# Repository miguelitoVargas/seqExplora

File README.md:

# seqExplora
modulos tarjetas kicad

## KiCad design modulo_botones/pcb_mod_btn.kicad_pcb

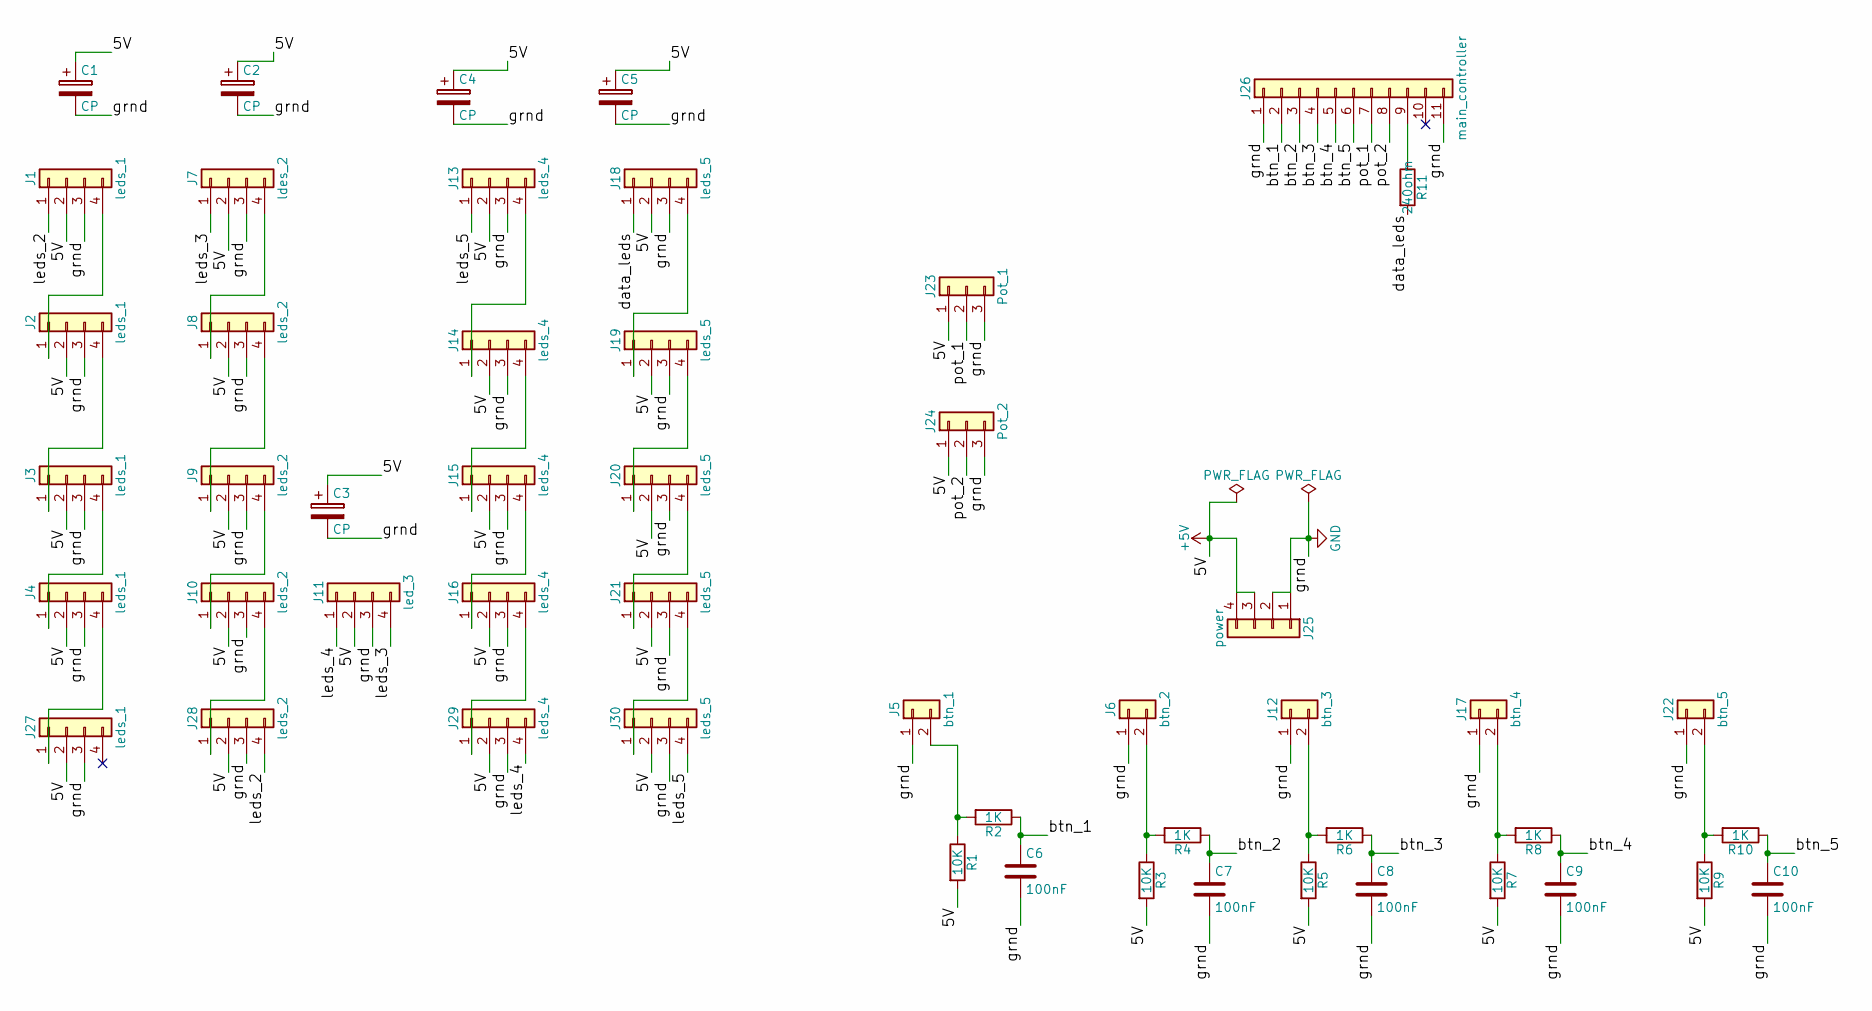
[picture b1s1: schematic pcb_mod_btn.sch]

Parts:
C1, C2, C3, C4, C5: CP; CP_Radial_D8.0mm_P5.00mm
C6, C7, C8, C9, C10: 100nF; C_0805_HandSoldering
J1, J2, J3, J4, J27: leds_1; Pin_Header_Straight_1x04_Pitch2.54mm
J5: btn_1; Pin_Header_Straight_1x02_Pitch2.54mm
J6: btn_2; Pin_Header_Straight_1x02_Pitch2.54mm
J7: ldes_2; Pin_Header_Straight_1x04_Pitch2.54mm
J8, J9, J10, J28: leds_2; Pin_Header_Straight_1x04_Pitch2.54mm
J11: led_3; Pin_Header_Straight_1x04_Pitch2.54mm
J12: btn_3; Pin_Header_Straight_1x02_Pitch2.54mm
J13, J14, J15, J16, J29: leds_4; Pin_Header_Straight_1x04_Pitch2.54mm
J17: btn_4; Pin_Header_Straight_1x02_Pitch2.54mm
J18, J19, J20, J21, J30: leds_5; Pin_Header_Straight_1x04_Pitch2.54mm
J22: btn_5; Pin_Header_Straight_1x02_Pitch2.54mm
J23: Pot_1; Pin_Header_Straight_1x03_Pitch2.54mm
J24: Pot_2; Pin_Header_Straight_1x03_Pitch2.54mm
J25: power; TerminalBlock_bornier-4_P5.08mm
J26: main_controller; Pin_Header_Straight_1x11_Pitch2.54mm
R1, R3, R5, R7, R9: 10K; R_0805_HandSoldering
R2, R4, R6, R8, R10: 1K; R_0805_HandSoldering
R11: 240ohm; R_0805_HandSoldering

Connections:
+5V: C1.1, C2.1, C3.1, C4.1, C5.1, J1.2, J2.2, J3.2, J4.2, J7.2, J8.2, J9.2, J10.2, J11.2, J13.2, J14.2, J15.2, J16.2, J18.2, J19.2, J20.2, J21.2, J23.1, J24.1, J25.3, J25.4, J27.2, J28.2, J29.2, J30.2, R1.2, R3.2, R5.2, R7.2, R9.2
/btn_1: C6.1, J26.2, R2.1
/btn_2: C7.1, J26.3, R4.1
/btn_3: C8.1, J26.4, R6.1
/btn_4: C9.1, J26.5, R8.1
/btn_5: C10.1, J26.6, R10.1
/data_leds: J18.1, R11.2
/leds_2: J1.1, J28.4
/leds_3: J7.1, J11.4
/leds_4: J11.1, J29.4
/leds_5: J13.1, J30.4
/pot_1: J23.2, J26.7
/pot_2: J24.2, J26.8
GND: C1.2, C2.2, C3.2, C4.2, C5.2, C6.2, C7.2, C8.2, C9.2, C10.2, J1.3, J2.3, J3.3, J4.3, J5.1, J6.1, J7.3, J8.3, J9.3, J10.3, J11.3, J12.1, J13.3, J14.3, J15.3, J16.3, J17.1, J18.3, J19.3, J20.3, J21.3, J22.1, J23.3, J24.3, J25.1, J25.2, J26.1, J26.11, J27.3, J28.3, J29.3, J30.3
unnamed: J1.4, J2.1
unnamed: J2.4, J3.1
unnamed: J3.4, J4.1
unnamed: J5.2, R1.1, R2.2
unnamed: J6.2, R3.1, R4.2
unnamed: J7.4, J8.1
unnamed: J8.4, J9.1
unnamed: J9.4, J10.1
unnamed: J10.4, J28.1
unnamed: J12.2, R5.1, R6.2
unnamed: J13.4, J14.1
unnamed: J14.4, J15.1
unnamed: J15.4, J16.1
unnamed: J16.4, J29.1
unnamed: J17.2, R7.1, R8.2
unnamed: J18.4, J19.1
unnamed: J19.4, J20.1
unnamed: J20.4, J21.1
unnamed: J21.4, J30.1
unnamed: J22.2, R9.1, R10.2
unnamed: J26.9, R11.1
unnamed: J4.4, J27.1

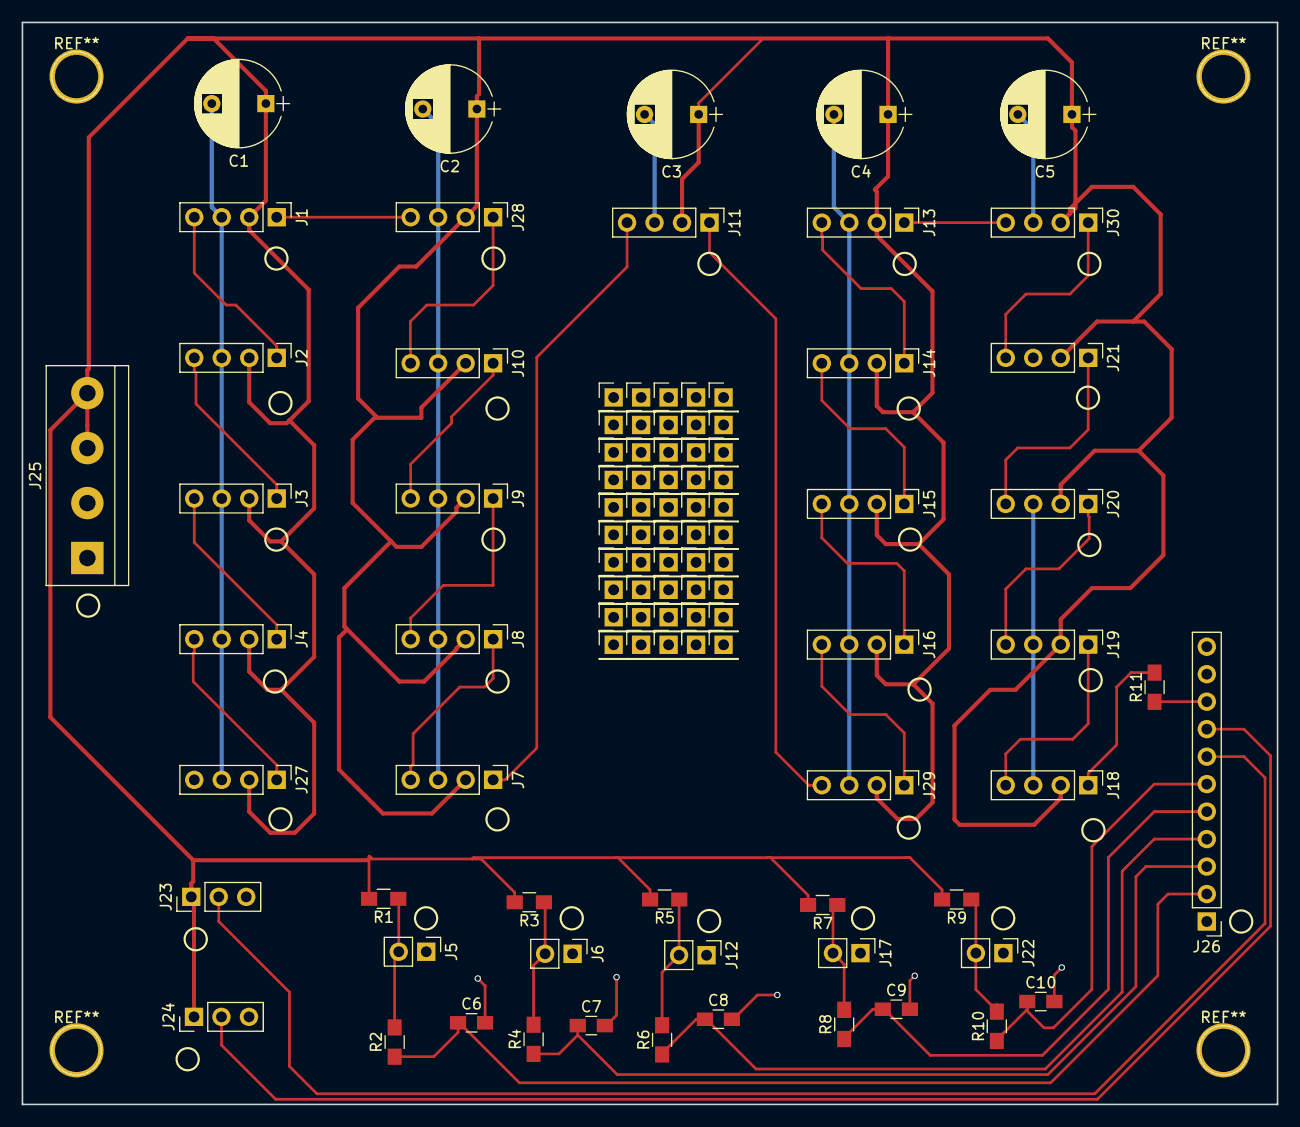
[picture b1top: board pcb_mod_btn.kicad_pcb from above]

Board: 2 copper layers, 116.0 x 100.0 mm, 51 parts (0 on the bottom side), 36 nets.

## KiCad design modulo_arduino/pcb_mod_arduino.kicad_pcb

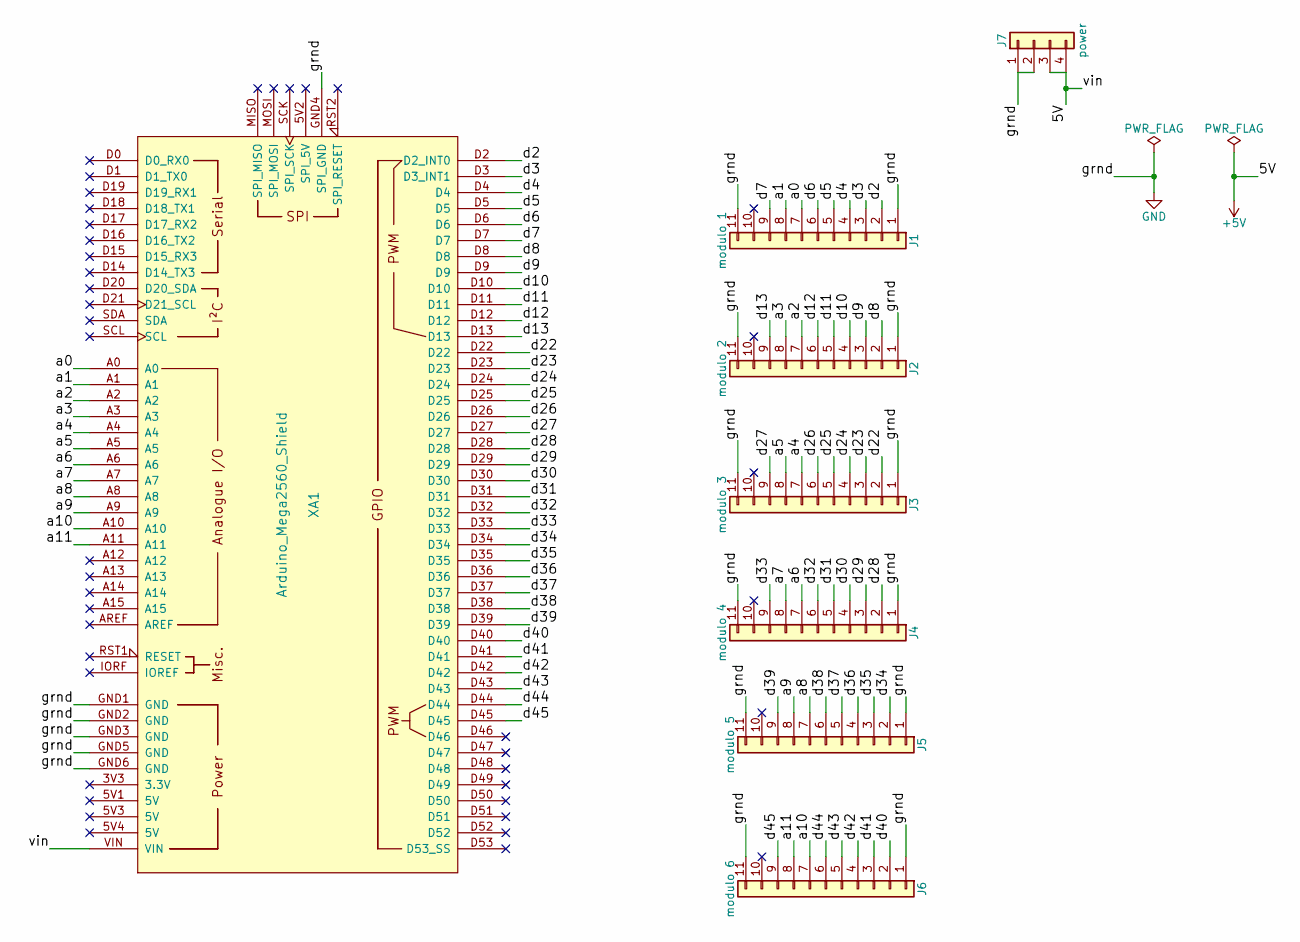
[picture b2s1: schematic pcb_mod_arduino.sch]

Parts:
J1: modulo 1; Pin_Header_Straight_1x11_Pitch2.54mm
J2: modulo 2; Pin_Header_Straight_1x11_Pitch2.54mm
J3: modulo 3; Pin_Header_Straight_1x11_Pitch2.54mm
J4: modulo 4; Pin_Header_Straight_1x11_Pitch2.54mm
J5: modulo 5; Pin_Header_Straight_1x11_Pitch2.54mm
J6: modulo 6; Pin_Header_Straight_1x11_Pitch2.54mm
J7: power; TerminalBlock_bornier-4_P5.08mm
XA1: Arduino_Mega2560_Shield

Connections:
+5V: J7.3, J7.4, XA1.VIN
/a0: J1.7, XA1.A0
/a1: J1.8, XA1.A1
/a2: J2.7, XA1.A2
/a3: J2.8, XA1.A3
/a4: J3.7, XA1.A4
/a5: J3.8, XA1.A5
/a6: J4.7, XA1.A6
/a7: J4.8, XA1.A7
/a8: J5.7, XA1.A8
/a9: J5.8, XA1.A9
/a10: J6.7, XA1.A10
/a11: J6.8, XA1.A11
/d2: J1.2, XA1.D2 (D2_INT0)
/d3: J1.3, XA1.D3 (D3_INT1)
/d4: J1.4, XA1.D4
/d5: J1.5, XA1.D5
/d6: J1.6, XA1.D6
/d7: J1.9, XA1.D7
/d8: J2.2, XA1.D8
/d9: J2.3, XA1.D9
/d10: J2.4, XA1.D10
/d11: J2.5, XA1.D11
/d12: J2.6, XA1.D12
/d13: J2.9, XA1.D13
/d22: J3.2, XA1.D22
/d23: J3.3, XA1.D23
/d24: J3.4, XA1.D24
/d25: J3.5, XA1.D25
/d26: J3.6, XA1.D26
/d27: J3.9, XA1.D27
/d28: J4.2, XA1.D28
/d29: J4.3, XA1.D29
/d30: J4.4, XA1.D30
/d31: J4.5, XA1.D31
/d32: J4.6, XA1.D32
/d33: J4.9, XA1.D33
/d34: J5.2, XA1.D34
/d35: J5.3, XA1.D35
/d36: J5.4, XA1.D36
/d37: J5.5, XA1.D37
/d38: J5.6, XA1.D38
/d39: J5.9, XA1.D39
/d40: J6.2, XA1.D40
/d41: J6.3, XA1.D41
/d42: J6.4, XA1.D42
/d43: J6.5, XA1.D43
/d44: J6.6, XA1.D44
/d45: J6.9, XA1.D45
GND: J1.1, J1.11, J2.1, J2.11, J3.1, J3.11, J4.1, J4.11, J5.1, J5.11, J6.1, J6.11, J7.1, J7.2, XA1.GND1 (GND), XA1.GND2 (GND), XA1.GND3 (GND), XA1.GND4 (SPI_GND), XA1.GND5 (GND), XA1.GND6 (GND)

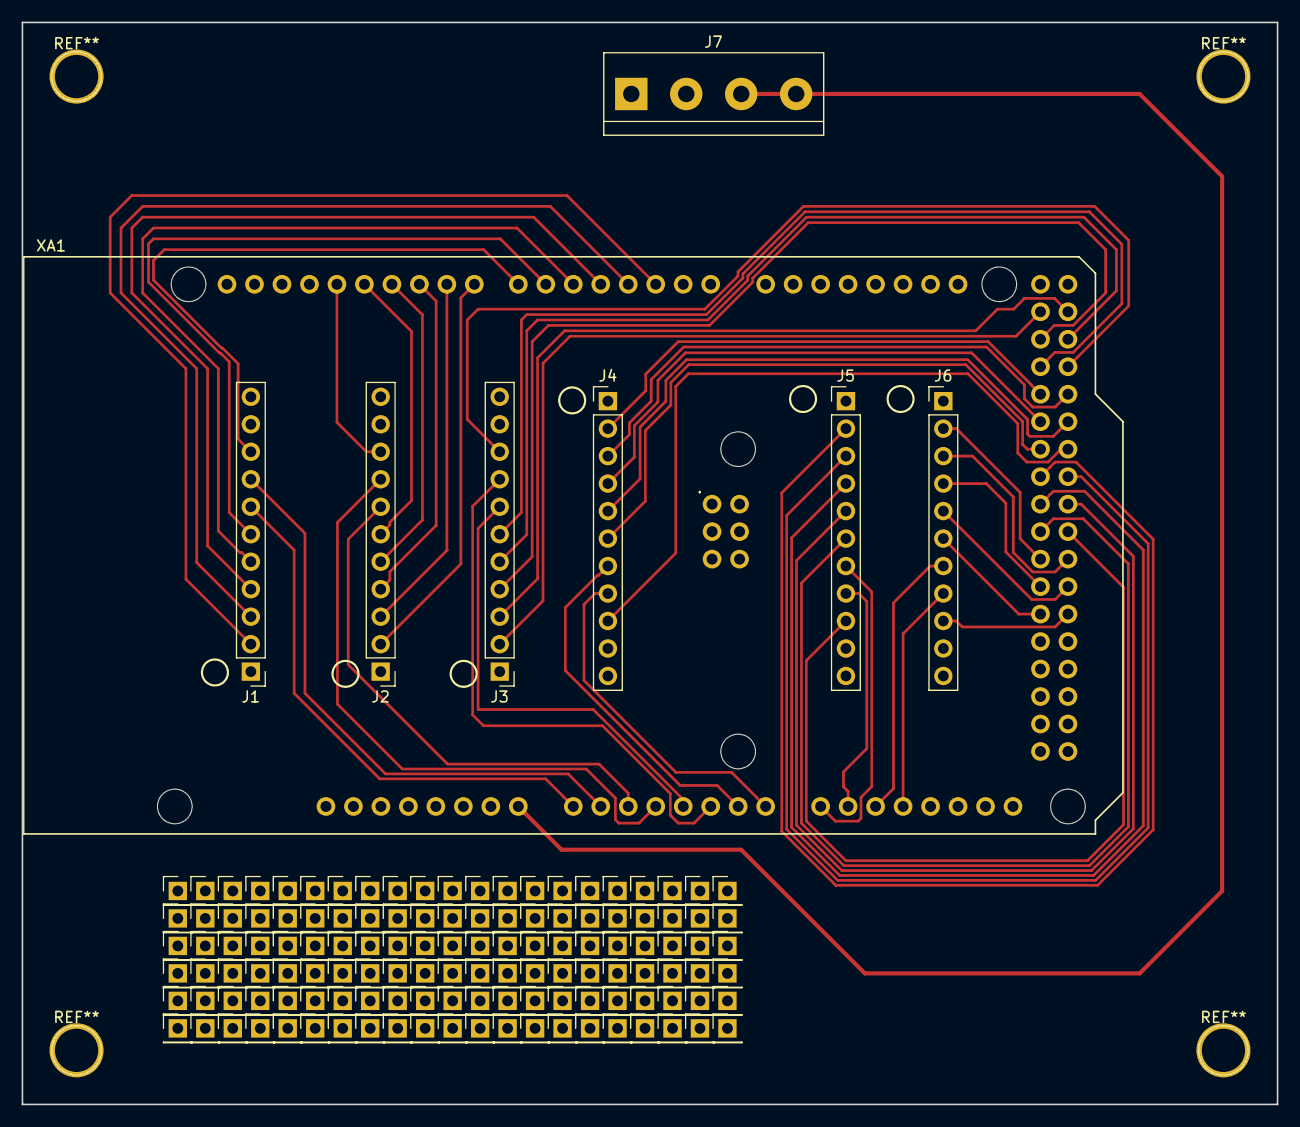
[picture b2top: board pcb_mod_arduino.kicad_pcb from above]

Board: 2 copper layers, 116.0 x 100.0 mm, 8 parts (0 on the bottom side), 50 nets.

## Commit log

2018-06-15 esquematico primeras opciones de ruteo
2018-06-16 footprints para tornillos, modulo botones terminado, todo marcas pin 1 headers
2018-06-17 pcb arduino ok, revisar pitch pines independientes
2018-06-18 marcas en pin #1 de headers, primer gerber export :3
2018-06-18 marcas pines, reemplazo borneras, orientacion, separacion headers, ubicacion arduino
2018-06-20 marcas botones ok, gerber exports ultima version
